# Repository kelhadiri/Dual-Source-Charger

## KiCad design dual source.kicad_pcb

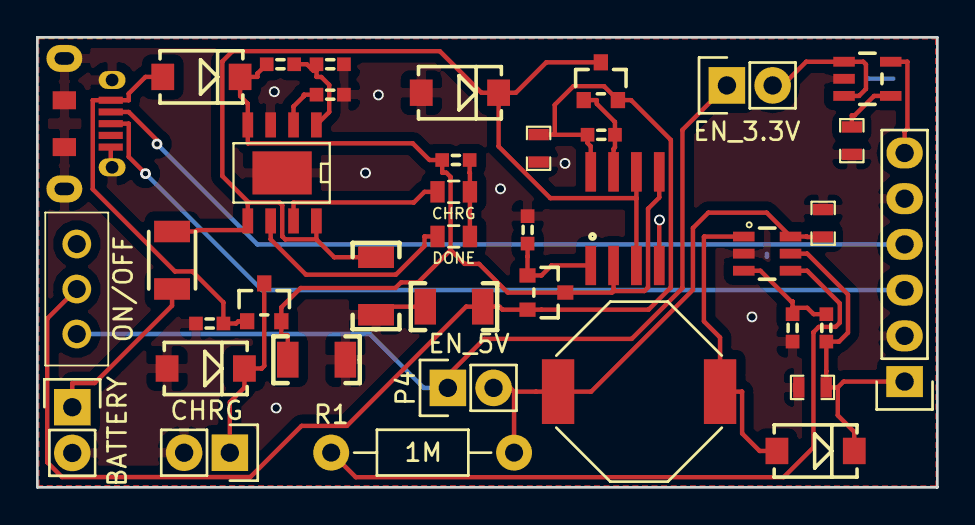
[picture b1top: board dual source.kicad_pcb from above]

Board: 2 copper layers, 50.0 x 25.0 mm, 39 parts (0 on the bottom side), 25 nets.

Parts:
C1: 10uF; 0603_CAP
C2: 100nF; 0603_CAP
C3: 22uF; 0603_CAP
C201, C204: 10uF 16V; 1210_CAP
C202: 100nF 16V; 0603_CAP
C203: 100uF 16V X5R; 1210_CAP
D1, D2, D3, D201: SS14; DIODE_SMA
F1: 1A PTC; 1210
L1: 2.2uH; IND_SRU1038
LED201: DONE; 0805
LED202: CHRG; 0805
P1: BATTERY; Pin_Header_Straight_1x02
P2: CHRG; Pin_Header_Straight_1x02
P3: USB_5PIN_SHELL; USB-MICRO-5pin_PTHMOUNT
P4: EN_5V; Pin_Header_Straight_1x02
P5: EN_3.3V; Pin_Header_Straight_1x02
P6: CONN_01X06; Pin_Header_Straight_1x06
Q201, Q202, Q203: FDN340P; SOT23_FET
R1: 1M; Resistor_Horizontal_RM10mm
R2: 95.3K; 0603
R3: 30.9K; 0603
R4, R5: 100K; 0603
R201, R202: 1K; 0603
R204, R205: 7.15K 1%; 0603
SW1: ON/OFF; SS12D00
TH201: 10K NTC; 0603
U1: SPX3819M5-3.3; SOT23-5
U2: LTC3426; SOT23-6
U201: CN3063; CN3063_SOIC8_EP
U202: MCP6002; SO08_4mm

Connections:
+3V3: P6.6, U1.5
+5V: C3.1, D3.K, P6.1, R2.1, U2.5
/BAT+: F1.1, P1.1
/Power/GBAT: Q203.G, R5.2, U202.7
/Power/GIN: Q202.G, R4.1, U202.1
/Power/SOLAR_IN: D1.K, P2.1, Q201.D
/Power/USB_IN: D201.A, P3.1, Q201.G, R201.1
/Power/VBAT: C204.1, D2.K, F1.2, Q203.D, U201.5, U201.8, U202.3, U202.6
/Power/VIN: C201.1, D201.K, Q201.S, Q202.D, R202.1, R205.1, U201.4, U202.2, U202.5
/Power/VOUT: C202.1, C203.2, Q202.S, Q203.S, R5.1, SW1.2, U202.8
/Power/~CHRG: LED202.1, U201.7
/Power/~DONE: LED201.1, U201.6
/USB_D+: P3.3, P6.3
/USB_D-: P3.2, P6.4
/VOUT: P4.1, P5.1, SW1.1
GND: C1.2, C2.2, C3.2, C201.2, C202.2, C203.1, C204.2, D1.A, D2.A, P1.2, P2.2, P3.5, P3.SHLD, P6.2, P6.5, R3.2, R4.2, R201.2, R204.2, TH201.2, U1.2, U2.2, U201.3, U201.PAD, U202.4
unnamed: C1.1, L1.1, P4.2, R1.2, U2.6
unnamed: C2.1, U1.4
unnamed: D3.A, L1.2, U2.1
unnamed: LED201.2, LED202.2, R202.2
unnamed: P5.2, U1.1, U1.3
unnamed: R1.1, U2.4
unnamed: R2.2, R3.1, U2.3
unnamed: R204.1, U201.2
unnamed: R205.2, TH201.1, U201.1

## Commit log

2016-03-18 :tada: Added .gitattributes & .gitignore files
2016-03-18 Updated Power Circuit.
2016-03-23 Board design Attempt 1
2016-03-23 Changed file Power.sch to power.sch for compatability. Redid FTLib submodule because it wouldn't init properly. Git client difference?
2016-06-01 Added photo
2016-06-01 Added Board V1 screenshot

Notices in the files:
dual source.kicad_pcb:
TAPR Open Hardware License
